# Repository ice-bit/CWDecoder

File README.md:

# CWDecoder

CWDecoder is a realtime _morsecode-to-ascii_ translator
for ATMega µC written in C.

<div align="center">
    
</div>

## Building
PCB layout has been tested and it's ensured that it works, if you wanna buy a copy of 
this decoder, compress _gerbers_ directory(`pcb/gerbers`) in a `zip` file and build it
from your favourite PCB manufacturing company(may i suggest you [JLCPCB](https://jlcpcb.com/)?).  
**NOTE**: PCB manufacturing companies will sell you just the circuit boards, **WITHOUT** any components on it, so you still need to buy elsewhere [components](#component-list) and solder them manually.

The code provided in this repository is adapted to the schematics, but it can be changed (for instance pin number of I/O devices) according to your needs.

### Schematics
KiCAD `.pro` project file can be found into `pcb` directory.  

<div align="center">

</div>

### Component list
To build this project you will need the following components:  
- x4 470Ohm resistor;  
- x1 3.3kOhm resistor;  
- x1 3.5mm AudioJack connector;  
- x1 LCD1602 liquid crystal display;  
- x1 Arduino nano;
- x1 buzzer(maximum size: 12.2x6.5mm)  
- x1 push button

### Software
**NOTE:** In order to build it you will need the 
[Arduino SDK](https://www.arduino.cc/en/main/software) and the [LiquidCrystal Library](https://www.arduino.cc/en/Reference/LiquidCrystal).  
CWDecoder works in a very simple way, it constantly check if _button state_ has changed:
```c
    ...
    key.currentState = digitalRead(key.pin); // Retrieve key status
    if(key.currentState != key.prevState) {
        if(key.currentState == HIGH) { // If button state is HIGH
            // Start to beep and power on LED
            ...
            key.counter = millis(); // Record when button has been pressed
        } else if(key.currentState == LOW) {
            // If button has been released, then determines if it is a 'dit' or 'dat'.
        }
    }
```
 if so it determines whether the input is of _long_(ie a 'dah') or _short_ type(ie a 'dit'); to do so, when the button is released, it checks if _active time_(ie time when straight key is pressed)
 is greater than two constant fixed time(`shortPress` and `longPress`):
 ```c
    ...
    uint64_t currentTime = millis(); // Get current time
    // If button has been pressed enough time for a dit...
    if(((currentTime - key.counter) >= shortPress) && (currentTime - key.counter))
        buttonEvent(0); // ...Handle a dit
    else if((currentTime - key.counter) >= longPress) // Otherwise
        buttonEvent(1); // Handle a dat
    ...
 ```
At this point it calls `buttonEvent()` function, which add the proper symbol(ie a dot or a line) to a fixed size char buffer:
```c
    void buttonEvent(uint8_t type_of_event) {
        if(type_of_event == 0) // Short press
            buf[++pos] = '.';
        else if(type_of_event == 1) // Long press
        buf[++pos] = '-';
    }
```

Last but not least, after last function has returned, it sample the buffer if and only a certain amount of time
has passed. Without this mechanism, for instance, the program would not distinguish
between the letter 'e'(a single `dit` in morse code) and the letter 's'(three `dit` in morse code):
```c
    const short wpm = 500; // Words-per-minute 
     // If user hasn't touched key for enough time, then we can sample the buffer
    if((millis() - timeLast) > wpm)
        translate();
```
**NOTE**: words-per-minute value is **NOT** accurate, i found out that `500` is something like `~24wpm`.  
`translate()` function does the following:
```c
    char translatedWord = converter(buf); // Convert what's inside the buffer
    ...
    lcd.print(translatedWord); // Print ASCII character into the LCD.
```
After each letter has been translated, it empty the buffer to prevent buffer overflow.
In this way it's possible to use a tiny char buffer and save a lot of precious memory:
```c
    memset(buf, 0, sizeof(buf)); // reset buffer
    pos = -1; // Set index at the beginning
```

### Character support
By default CWDecoder support international alphabet(ie English alphabet) + 0-9 numbers. If you need special characters
(such as comma, period, blockquote, etc.) you can add them by adding new entry on `converter()` function:
```c
    ...
     else if(!strcmp(ch, "<morse_code>")) { return '<ascii_letter>'; }
    ...
```

## License
This project is been released under 
[GPLv3](https://choosealicense.com/licenses/gpl-3.0/) license.

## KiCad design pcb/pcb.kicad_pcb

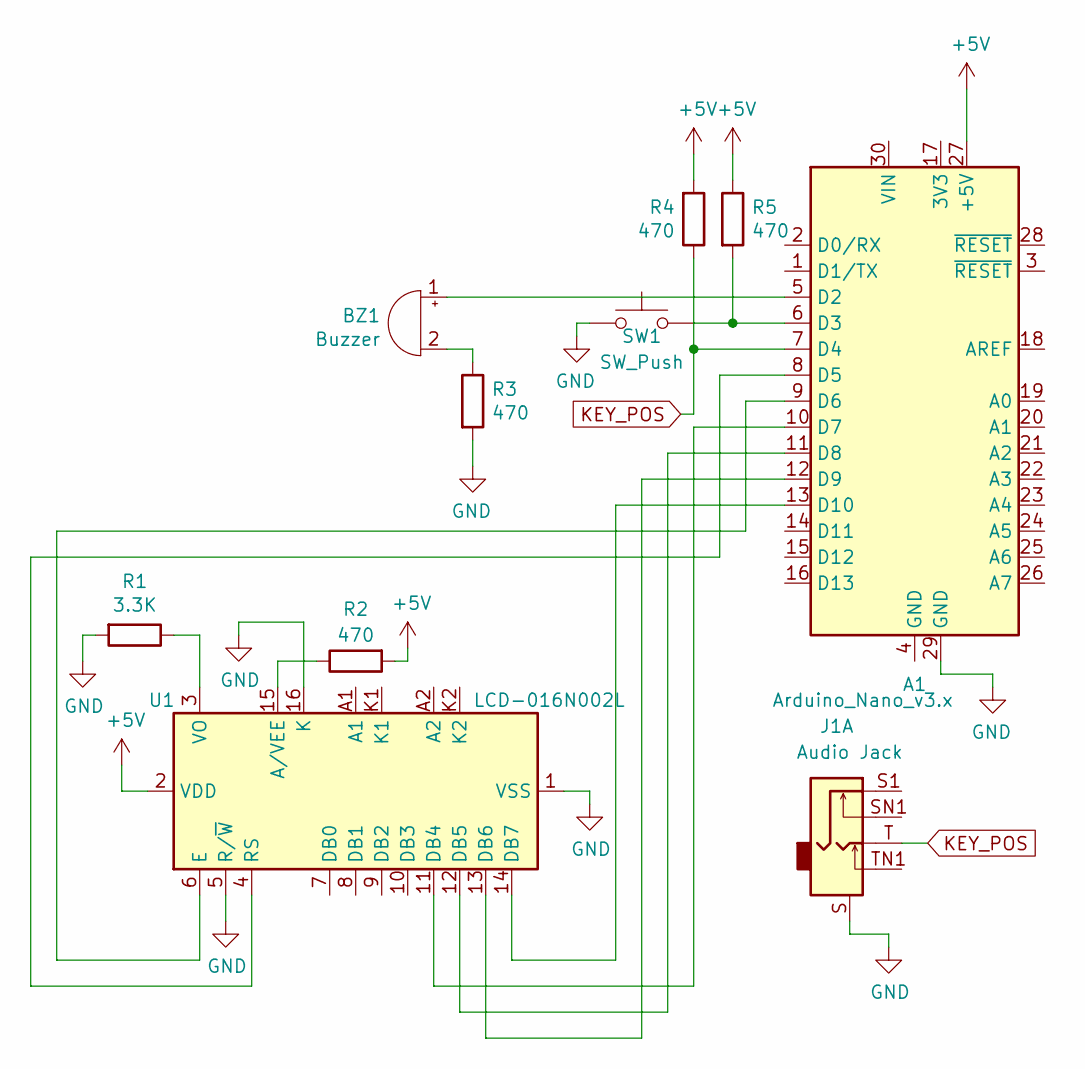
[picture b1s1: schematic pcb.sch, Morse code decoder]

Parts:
A1: Arduino_Nano_v3.x; Arduino_Nano
BZ1: Buzzer; Buzzer_TDK_PS1240P02BT_D12.2mm_H6.5mm
J1: Audio Jack; Jack_3.5mm_Ledino_KB3SPRS_Horizontal
R1: 3.3K; R_Axial_DIN0207_L6.3mm_D2.5mm_P15.24mm_Horizontal
R2, R3, R4, R5: 470; R_Axial_DIN0207_L6.3mm_D2.5mm_P15.24mm_Horizontal
SW1: SW_Push; SW_PUSH_6mm_H4.3mm
U1: LCD-016N002L; WC1602A

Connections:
+5V: A1.27 (+5V), R2.2, R4.2, R5.1, U1.2 (VDD)
GND: A1.29 (GND), J1.S, R1.2, R3.2, SW1.1, U1.1 (VSS), U1.5 (R/~W), U1.16 (K)
KEY_POS: A1.7 (D4), J1.T, R4.1
unnamed: A1.5 (D2), BZ1.1 (-)
unnamed: A1.6 (D3), R5.2, SW1.2
unnamed: A1.8 (D5), U1.4 (RS)
unnamed: A1.9 (D6), U1.6 (E)
unnamed: A1.10 (D7), U1.11 (DB4)
unnamed: A1.11 (D8), U1.12 (DB5)
unnamed: A1.12 (D9), U1.13 (DB6)
unnamed: A1.13 (D10), U1.14 (DB7)
unnamed: BZ1.2 (+), R3.1
unnamed: R1.1, U1.3 (VO)
unnamed: R2.1, U1.15 (A/VEE)

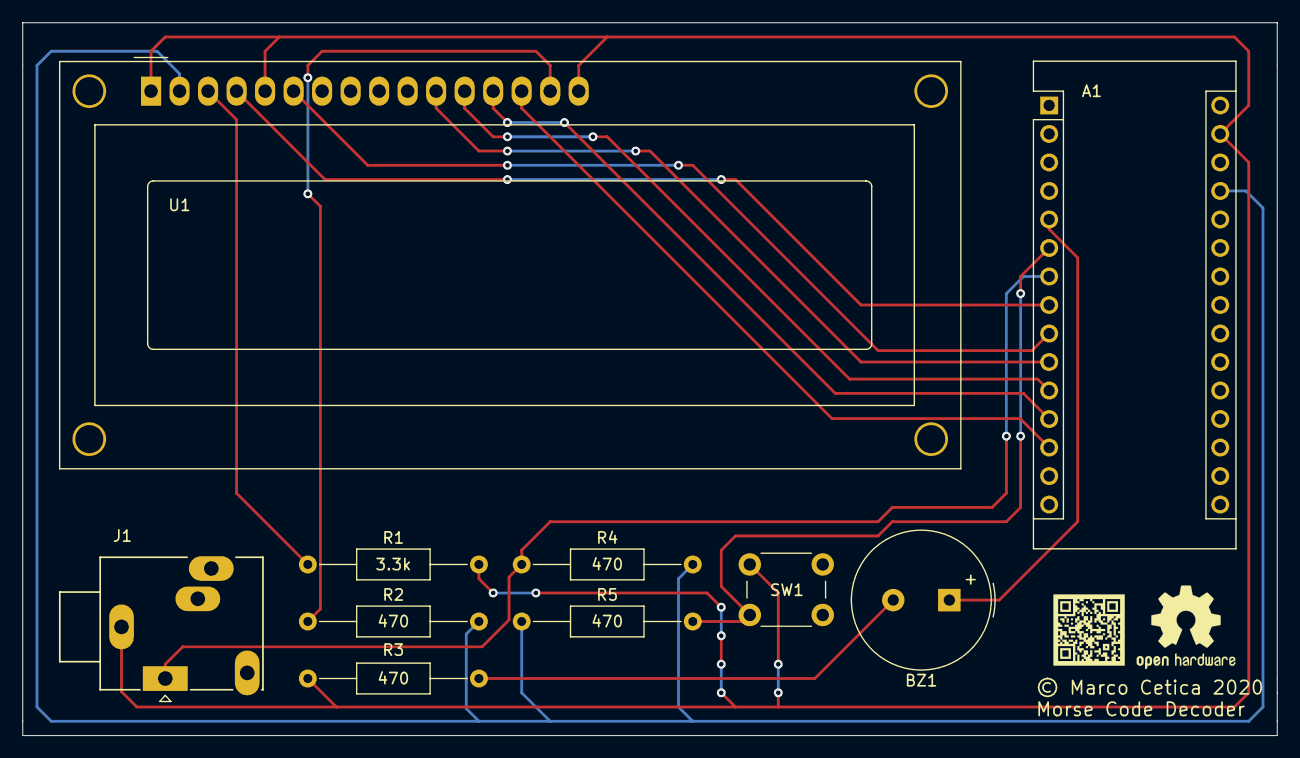
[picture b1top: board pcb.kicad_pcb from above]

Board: 2 copper layers, 111.8 x 63.5 mm, 10 parts (0 on the bottom side), 14 nets.

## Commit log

2020-05-16 First upload
2020-05-21 Reading data from a straight key input
2020-05-21 Added tone generator
2020-05-21 Fixed a strange bug
2020-05-29 Split words according to timing
    The program is now able to split the input
    according on how much time has passed since
    the last keystroke. This approach is not
    very optimized and potential faulty
    for production, though.
2020-05-29 Added comments and improved mem usage
2020-05-30 Fixed a bug about spaces
    CWDecoder is now able to add spaces
    between words at the end of a word
    rather than at the beginning of a new
    one.
2020-05-30 Decoding finally works!
2020-05-30 Added lcd support
2020-05-30 Added License and Readme
2020-05-31 Fixed LCD bug and added reset button
2020-06-04 Updated repo structure for Arduino Pro IDE
2020-06-04 Added schematics
2020-06-05 Completed schematics
2020-06-08 Finished schematics and added pcb layout
2020-06-08 Finished pcb wiring
2020-06-09 Redesigned pcb due to a bug
2020-06-10 rewired pcb
2020-06-10 Updated gitignore
2020-06-10 Added kicad library
2020-06-11 Update pin numbers
2020-06-13 Updated a footprint
2020-06-14 Added gerbers
2020-06-22 Added a documentation and removed useless code

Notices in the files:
pcb/pcb.kicad_pcb:
© Marco Cetica 2020
